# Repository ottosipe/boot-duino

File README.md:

boot-duino
==========

Arduino-based research project at the University of Michigan. Focusing on an open-source solution to gait and posture analysis.

## Project Status as of Sept. 30, 2013
- Hardware 3.0 is stable
- Software can collect, save, or transmit IMU data.
- Case is designed and being tested.

## Programming

- Program Upload via BT: `make upload`
- Program Upload via AVRisp mkII: `make program`
- Bootloader: `make bootload`
- Fuses: `make fuses`

----

Bluetooth Settings:  
`ST,255` 	- command timer  
`SU,38` 	- baud rate 38400  
`S~,3` 		- Set Modem Profile   

Fuse Info: [Arduino Fuses](http://www.codingwithcody.com/2011/04/arduino-default-fuse-settings/), [Fuse Calculator](http://www.engbedded.com/fusecalc/)

----

Hardware Notes

- Chip Select Pin : D5

----

Install Arduino-Makefile:  

```
sudo perl -MCPAN -e shell
	install YAML
	install Device::SerialPort
```

## Resources and Libraries:
 
- [I2CDev](https://github.com/jrowberg/i2cdevlib)
- [SDFat](http://code.google.com/p/sdfatlib/downloads/list)
- [Arduino-Makefile](https://github.com/mjoldfield/Arduino-Makefile)

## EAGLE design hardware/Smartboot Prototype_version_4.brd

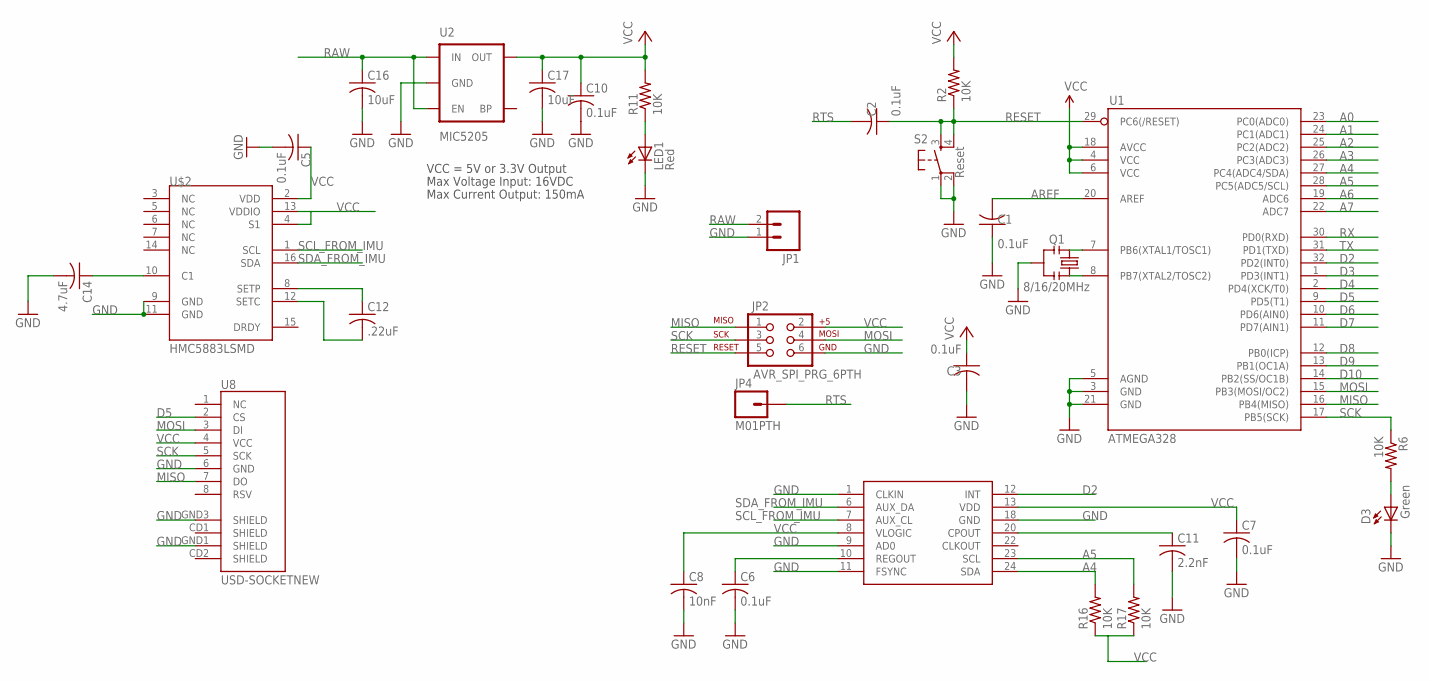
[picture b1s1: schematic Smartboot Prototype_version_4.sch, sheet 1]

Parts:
C1, C2, C3, C5, C6, C7, C10: 0.1uF; C0603
C8: 10nF; C0603
C11: 2.2nF; C0603
C12: .22uF; C0603
C14: 4.7uF; C0603
C16, C17: 10uF; C0603
D3: Green; LED-0603
JP1: M02-JST-2MM-SMT; JST-2-SMD
JP2: AVR_SPI_PRG_6PTH; 2X3
JP4: M01PTH; 1X01
LED1: Red; LED-0603
Q1: 8/16/20MHz; RESONATOR-SMD
R2, R6, R11, R16, R17: 10K; R0603
S2: Reset; TACTILE_SWITCH_SMD
U1: ATMEGA328; TQFP32-08
U2: MIC5205; SOT23-5
U8: USD-SOCKETNEW; MICRO-SD-SOCKET-PP
U$2: HMC5883LSMD; 16LPCC
U$5: MPU-6050A; QFN-24-NP

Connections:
A0: U1.23 (PC0(ADC0))
A1: U1.24 (PC1(ADC1))
A2: U1.25 (PC2(ADC2))
A3: U1.26 (PC3(ADC3))
A4: R16.2, U1.27 (PC4(ADC4/SDA)), U$5.24 (SDA)
A5: R17.2, U1.28 (PC5(ADC5/SCL)), U$5.23 (SCL)
A6: U1.19 (ADC6)
A7: U1.22 (ADC7)
AREF: C1.2, U1.20 (AREF)
D2: U1.32 (PD2(INT0)), U$5.12 (INT)
D3: U1.1 (PD3(INT1))
D4: U1.2 (PD4(XCK/T0))
D5: U1.9 (PD5(T1)), U8.2 (CS)
D6: U1.10 (PD6(AIN0))
D7: U1.11 (PD7(AIN1))
D8: U1.12 (PB0(ICP))
D9: U1.13 (PB1(OC1A))
D10: U1.14 (PB2(SS/OC1B))
GND: C1.1, C3.2, C5.2, C6.2, C7.2, C8.2, C10.2, C11.2, C14.2, C16.2, C17.2, D3.C, JP1.1 (2), JP2.6, LED1.C, Q1.2, S2.1, S2.2, U1.3 (GND), U1.5 (AGND), U1.21 (GND), U2.2 (GND), U8.6 (GND), U8.GND1 (SHIELD), U8.GND3 (SHIELD), U$2.9 (GND), U$2.11 (GND), U$5.1 (CLKIN), U$5.9 (AD0), U$5.11 (FSYNC), U$5.18 (GND); also elsewhere on the board
MISO: JP2.1, U1.16 (PB4(MISO)), U8.7 (DO)
MOSI: JP2.4, U1.15 (PB3(MOSI/OC2)), U8.3 (DI)
unnamed: Q1.1, U1.8 (PB7(XTAL2/TOSC2))
unnamed: Q1.3, U1.7 (PB6(XTAL1/TOSC1))
unnamed: D3.A, R6.2
unnamed: C12.1, U$2.8 (SETP)
unnamed: C12.2, U$2.12 (SETC)
unnamed: C14.1, U$2.10 (C1)
unnamed: C6.1, U$5.10 (REGOUT)
unnamed: C11.1, U$5.20 (CPOUT)
unnamed: LED1.A, R11.1
RAW: C16.1, JP1.2 (1), U2.1 (IN), U2.3 (EN); also elsewhere on the board
RESET: C2.1, JP2.5, R2.1, S2.3, S2.4, U1.29 (PC6(/RESET))
RTS: C2.2, JP4.1; also elsewhere on the board
RX: U1.30 (PD0(RXD)); also elsewhere on the board
SCK: JP2.3, R6.1, U1.17 (PB5(SCK)), U8.5 (SCK)
SCL_FROM_IMU: U$2.1 (SCL), U$5.7 (AUX_CL)
SDA_FROM_IMU: U$2.16 (SDA), U$5.6 (AUX_DA)
TX: U1.31 (PD1(TXD)); also elsewhere on the board
VCC: C3.1, C5.1, C7.1, C8.1, C10.1, C17.1, JP2.2, R2.2, R11.2, R16.1, R17.1, U1.4 (VCC), U1.6 (VCC), U1.18 (AVCC), U2.5 (OUT), U8.4 (VCC), U$2.2 (VDD), U$2.4 (S1), U$2.13 (VDDIO), U$5.8 (VLOGIC), U$5.13 (VDD); also elsewhere on the board

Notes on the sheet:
Max Voltage Input: 16VDC
Max Current Output: 150mA
VCC = 5V or 3.3V Output

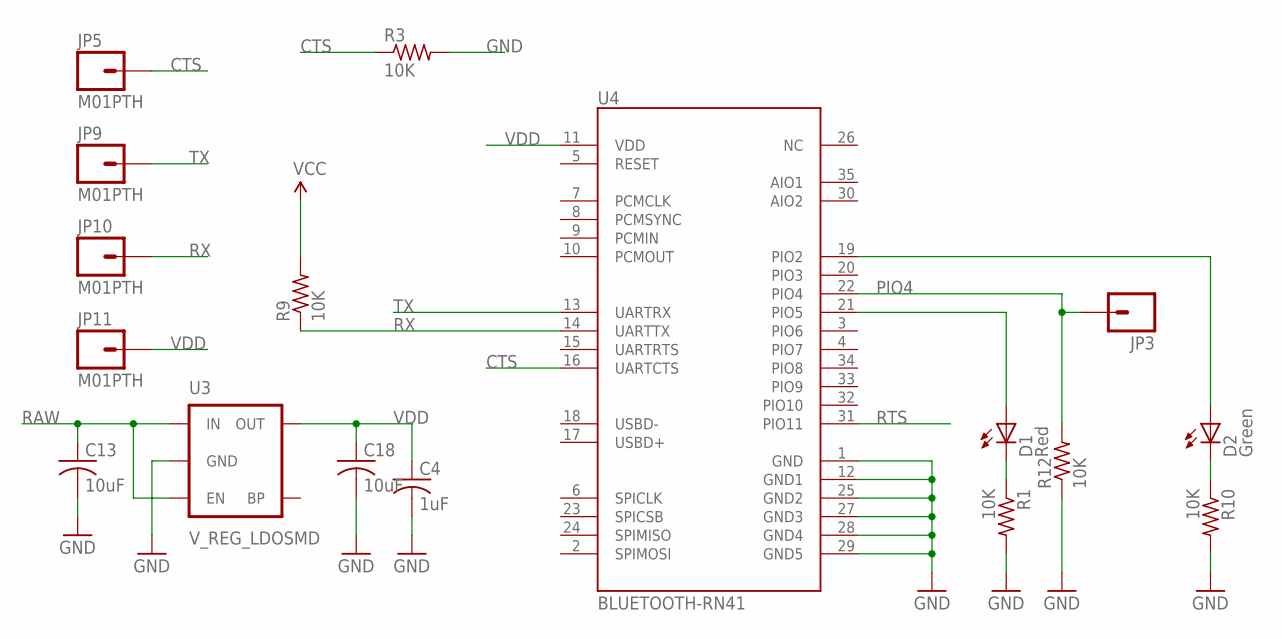
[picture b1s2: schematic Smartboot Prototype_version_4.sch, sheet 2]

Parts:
C4: 1uF; C0603
C13, C18: 10uF; C0603
D1: Red; LED-0603
D2: Green; LED-0603
JP3: M01SMDNS; 1X01NS
JP5, JP9, JP10, JP11: M01PTH; 1X01
R1, R3, R9, R10, R12: 10K; R0603
U3: V_REG_LDOSMD; SOT23-5
U4: BLUETOOTH-RN41; RN41

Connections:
CTS: JP5.1, R3.1, U4.16 (UARTCTS)
D1: D1.C, R1.1
D11: D2.C, R10.1
GND: C4.2, C13.2, C18.2, R1.2, R3.2, R10.2, R12.1, U3.2 (GND), U4.1 (GND), U4.12 (GND1), U4.25 (GND2), U4.27 (GND3), U4.28 (GND4), U4.29 (GND5); also elsewhere on the board
unnamed: D1.A, U4.21 (PIO5)
unnamed: D2.A, U4.19 (PIO2)
PIO4: JP3.1, R12.2, U4.22 (PIO4)
RAW: C13.1, U3.1 (IN), U3.3 (EN); also elsewhere on the board
RTS: U4.31 (PIO11); also elsewhere on the board
RX: JP10.1, R9.1, U4.14 (UARTTX); also elsewhere on the board
TX: JP9.1, U4.13 (UARTRX); also elsewhere on the board
VCC: R9.2; also elsewhere on the board
VDD: C4.1, C18.1, JP11.1, U3.5 (OUT), U4.11 (VDD)

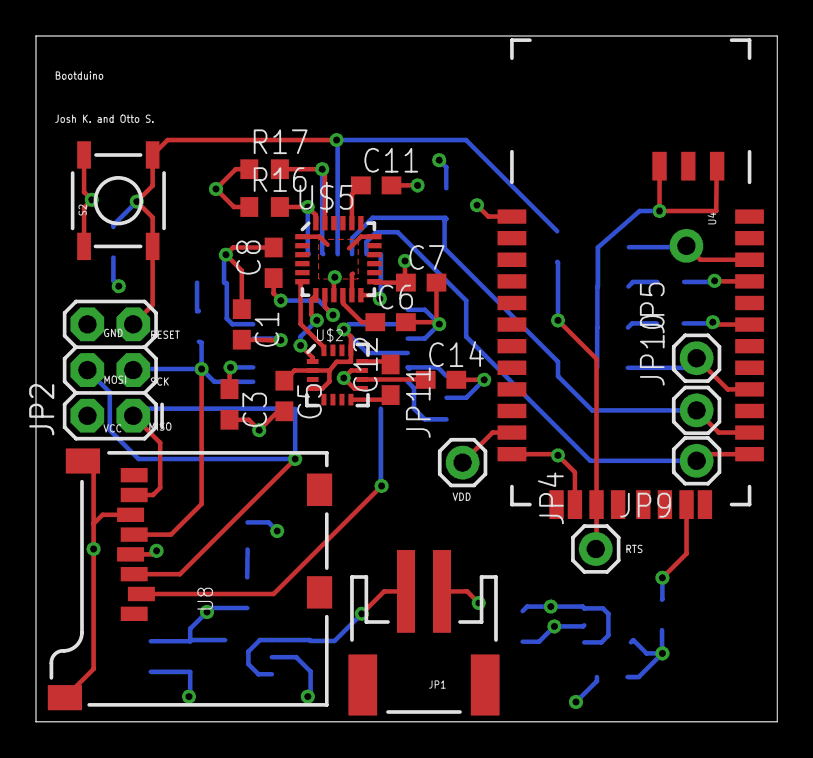
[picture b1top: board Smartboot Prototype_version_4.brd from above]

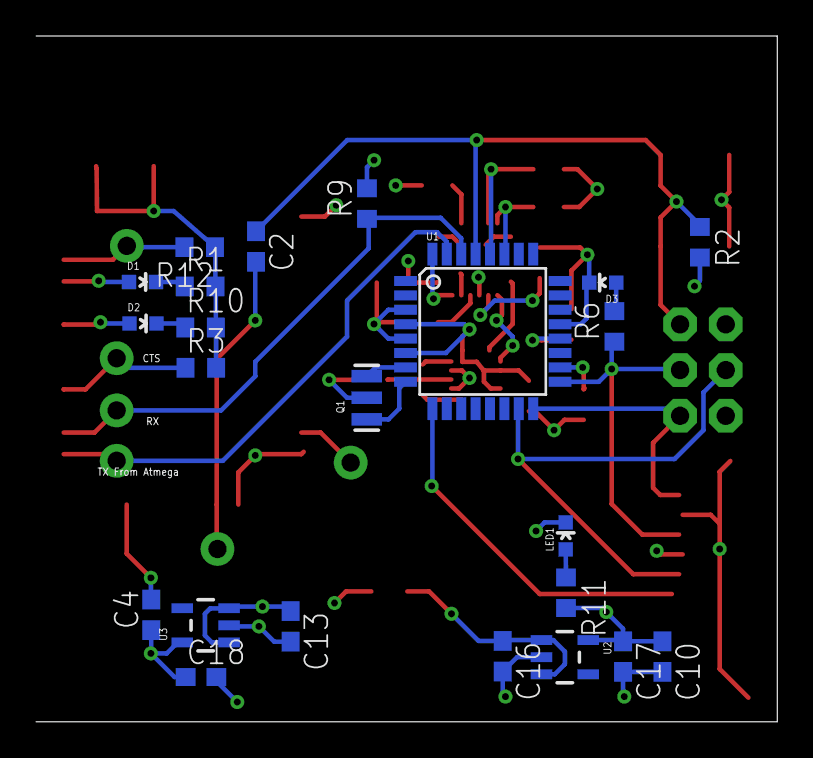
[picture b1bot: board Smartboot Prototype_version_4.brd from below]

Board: 4 copper layers, 41.2 x 38.1 mm, 47 parts (23 on the bottom side), 33 nets.

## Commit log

2013-02-11 initial commit with blink, wireless programming, avr-gcc, and makefile
2013-02-11 additions to readme
2013-03-11 added bootloader and BT settings
2013-03-13 working w/ new fuses
2013-03-16 working SD card, added hardware, added libs to makefiles
2013-03-18 added submodules, and fixed makefile
2013-03-18 rm old libs file
2013-03-18 readme update
2013-03-18 fixed includes, working SD and IMU demo
2013-04-03 fixed header file issues. start of new structure.
2013-04-06 quaternions and matlab
2013-04-15 world based accel, data collected
2013-06-02 makefile changes
2013-09-30 few project and software updates
2013-11-16 added case design

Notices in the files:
parts and their libraries:
SparkFun-Sensors: Licensing: CC v3.0 Share-Alike You are welcome to use this library for commercial purposes.
